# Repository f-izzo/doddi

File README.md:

# doddi

See the [instructions](https://github.com/Nimayer/doddi/blob/master/instructions.md) for details about usage.

##### Notes
When flashing software with Arduino-IDE, set the teensy clock to 16MHz or the Neopixels won't work

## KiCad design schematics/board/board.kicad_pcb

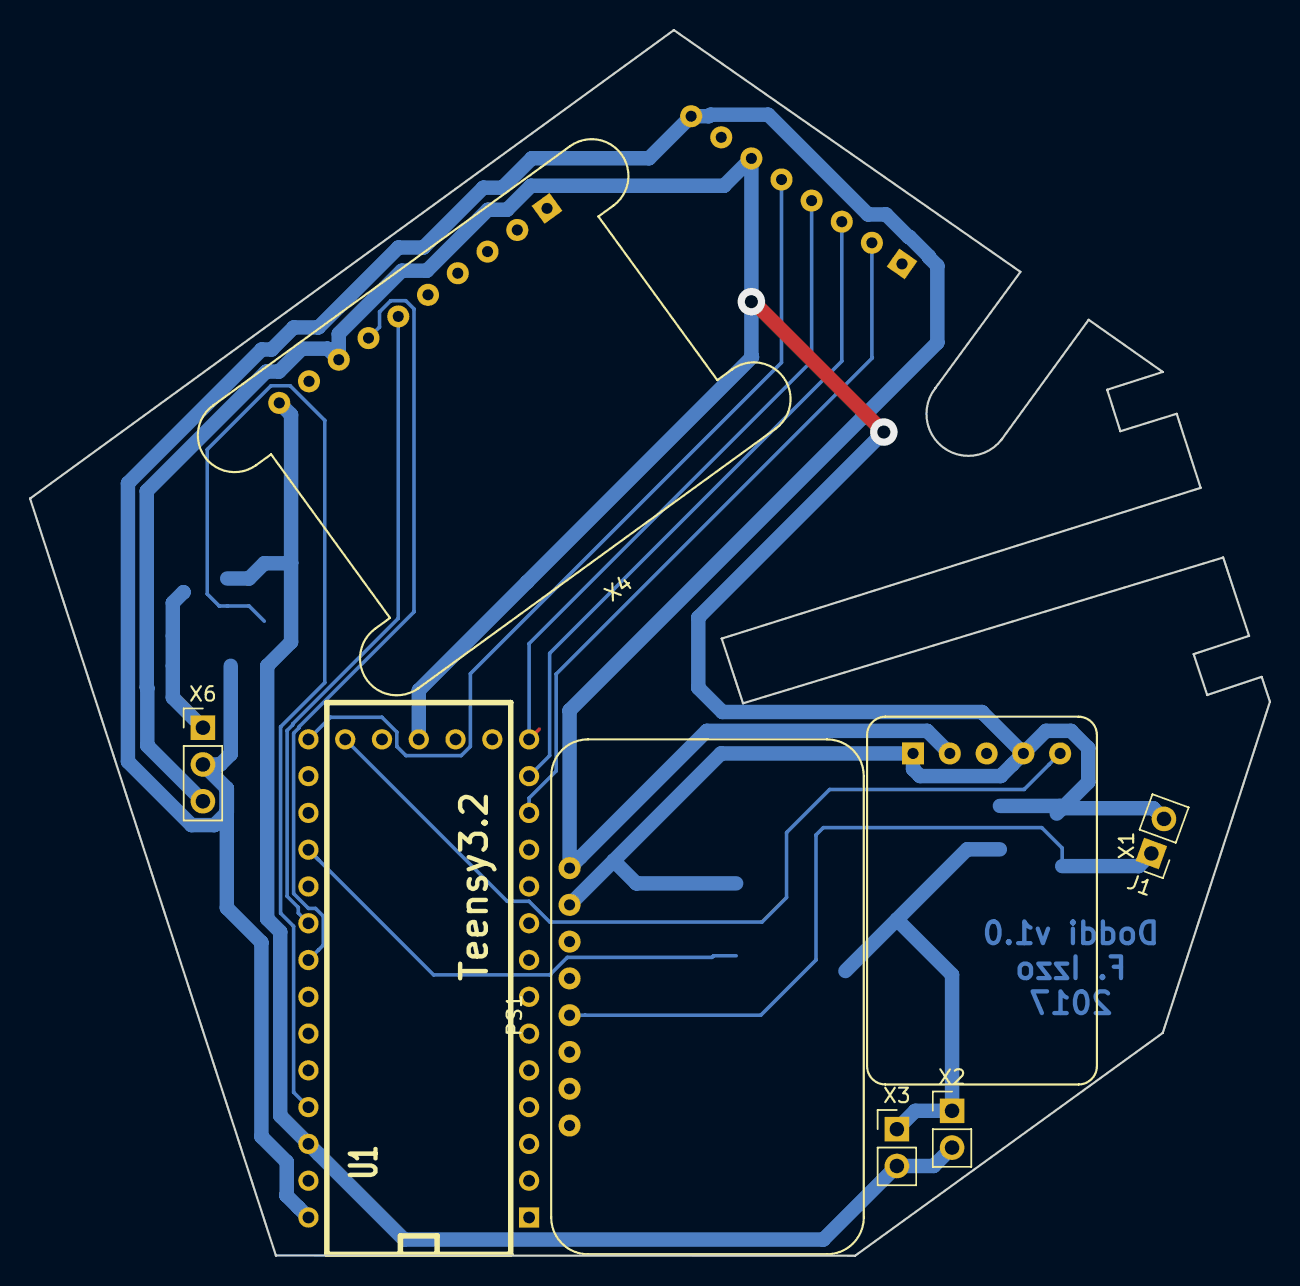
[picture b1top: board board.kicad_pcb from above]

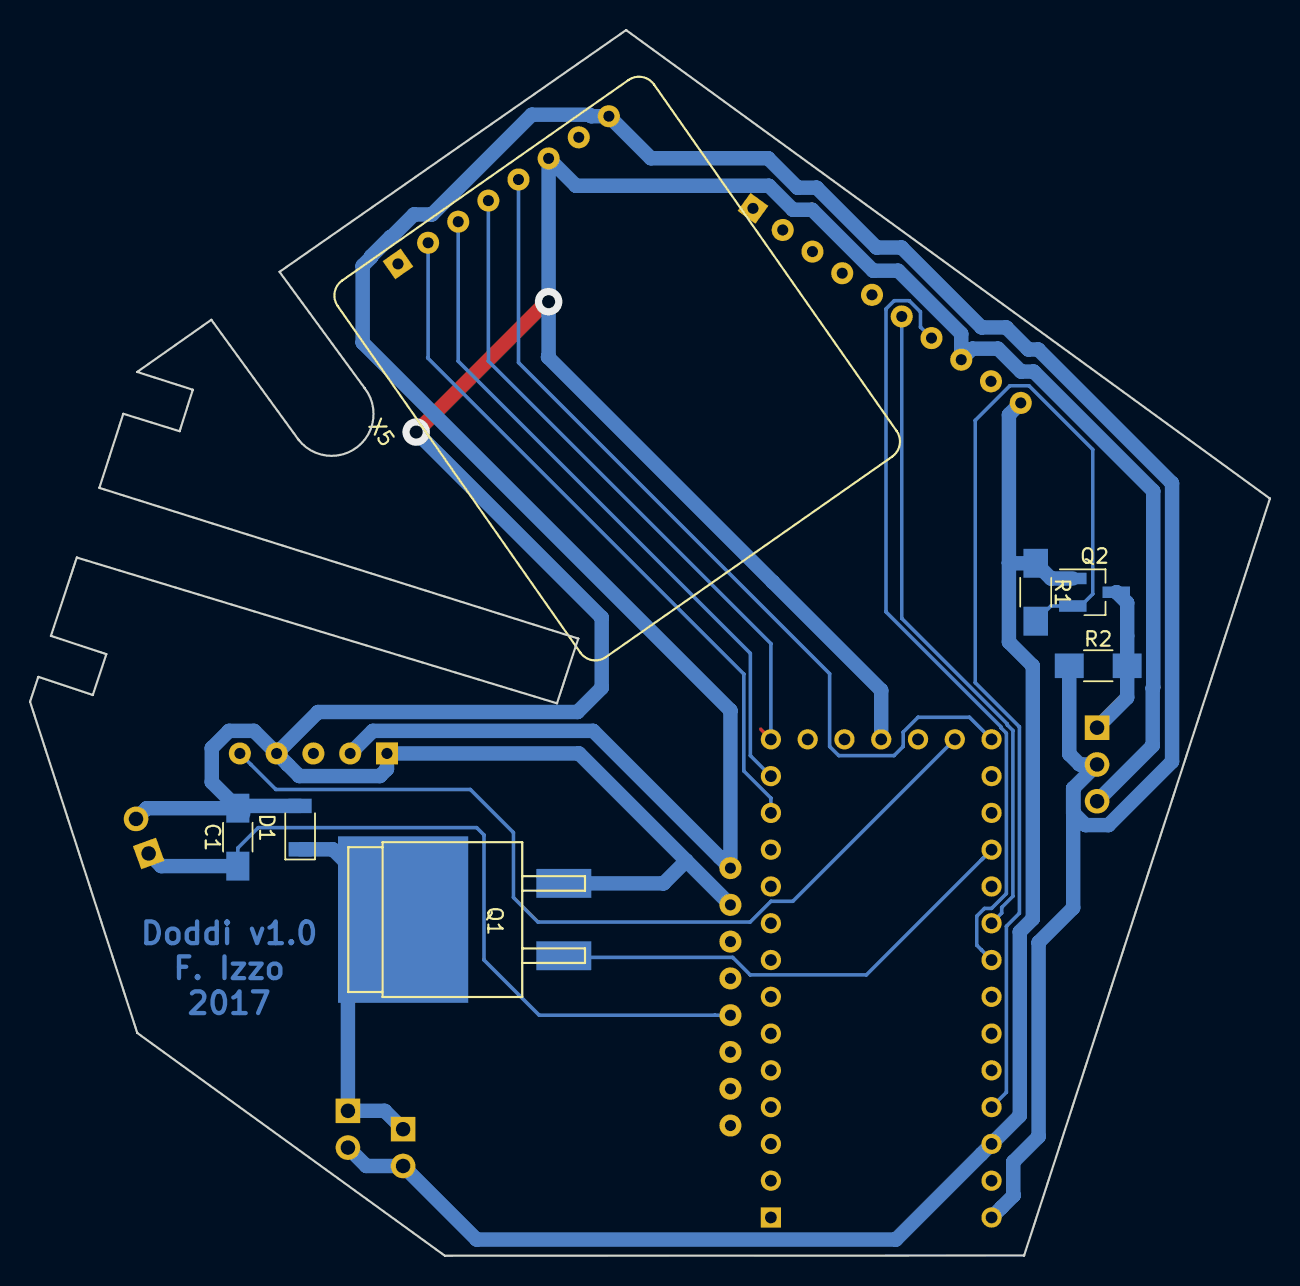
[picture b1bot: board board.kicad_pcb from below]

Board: 2 copper layers, 85.6 x 84.7 mm, 15 parts (7 on the bottom side), 15 nets.

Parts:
C1: C; C_1206_HandSoldering
D1: D; D_1206
J1: CONN_01X02; Pin_Header_Straight_1x02_Pitch2.54mm
PS1: AdafruitPowerboost500; adafruit_powerboost_500
Q1: Q_NMOS_GDS; SOT-404
Q2: Q_NMOS_GSD; SOT-23_Handsoldering
R1, R2: 33k; R_1206_HandSoldering
U1: Teensy3.2; TEENSY-3.2
X1: AdafruitPAM8302A; adafruit_PAM8302A
X2, X3: vibr_motor; Pin_Header_Straight_1x02_Pitch2.54mm
X4: AdafruitLSM303DLHC; adafruit_lsm303dlhc_accel
X5: Adafruit5VmicroSD; adafruit_5v_microsd_breakout
X6: NeopixelConn; Pin_Header_Straight_1x03_Pitch2.54mm

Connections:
+3V3: Q2.1, R1.1, U1.31, X2.2, X3.2, X4.1
+5V: PS1.8, R2.1, U1.33, X1.4, X5.8, X6.2
GND: C1.2, D1.2, J1.2, PS1.7, Q1.3, U1.17, X1.2, X1.5, X4.3, X5.6, X6.3
unnamed: C1.1, J1.1, PS1.4
unnamed: D1.1, Q1.2, X2.1, X3.1
unnamed: Q1.1, U1.23
unnamed: Q2.2, R1.2, U1.30
unnamed: Q2.3, R2.2, X6.1
unnamed: U1.12, X5.2
unnamed: U1.13, X5.3
unnamed: U1.14, X5.4
unnamed: U1.19, X1.1
unnamed: U1.20, X5.5
unnamed: U1.25, X4.5
unnamed: U1.26, X4.4

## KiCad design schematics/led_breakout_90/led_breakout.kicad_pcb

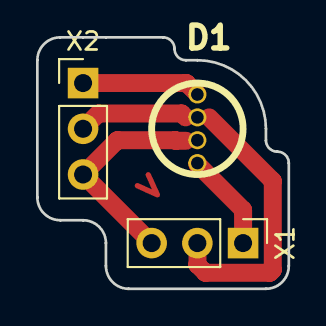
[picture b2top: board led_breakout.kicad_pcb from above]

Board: 2 copper layers, 14.0 x 14.0 mm, 3 parts (0 on the bottom side), 4 nets.

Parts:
D1: neopixel; LED5_RGB
X1, X2: NeopixelConn; Pin_Header_Straight_1x03_Pitch2.54mm

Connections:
+5V: D1.3, X1.2, X2.2
GND: D1.2, X1.3, X2.3
unnamed: D1.1, X1.1
unnamed: D1.4, X2.1

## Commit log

2017-03-19 Moved code, still untouched
2017-03-19 Removed endless loop when sdcard not present, removed empty lines across the program, temporary removed starting condition
2017-03-20 Now faces is a vector of structures instead of a matrix, general refactoring
2017-03-20 Updated software, lots of refactoring
2017-04-03 Added board projects
2017-05-01 Add accelerometer workaround, various fixes
2017-05-03 Major code refactoring, introducing threads
2017-05-03 Fixed problem with threads
2017-05-03 Rewritten face detection code
2017-05-03 Removed threads, changed saved face coordinates
2017-05-03 Fixed faces coordinates, finished face recognition
2017-05-04 Code refactoring, added shake detection
2017-05-04 Added finite state machine, fixed accelerometer hang
2017-05-04 added notes.txt with useful links
2017-05-04 Finished FSM structure
2017-05-04 Remove commented code, renamed FSM states
2017-05-04 Minor fixes
2017-05-05 Making sure state is not executed twice
2017-05-06 Neopixel fixes
2017-05-07 Final code commit
2017-05-07 Added images for instructions
2017-05-07 Scaled images
2017-05-18 Added missing libraries to the repository
